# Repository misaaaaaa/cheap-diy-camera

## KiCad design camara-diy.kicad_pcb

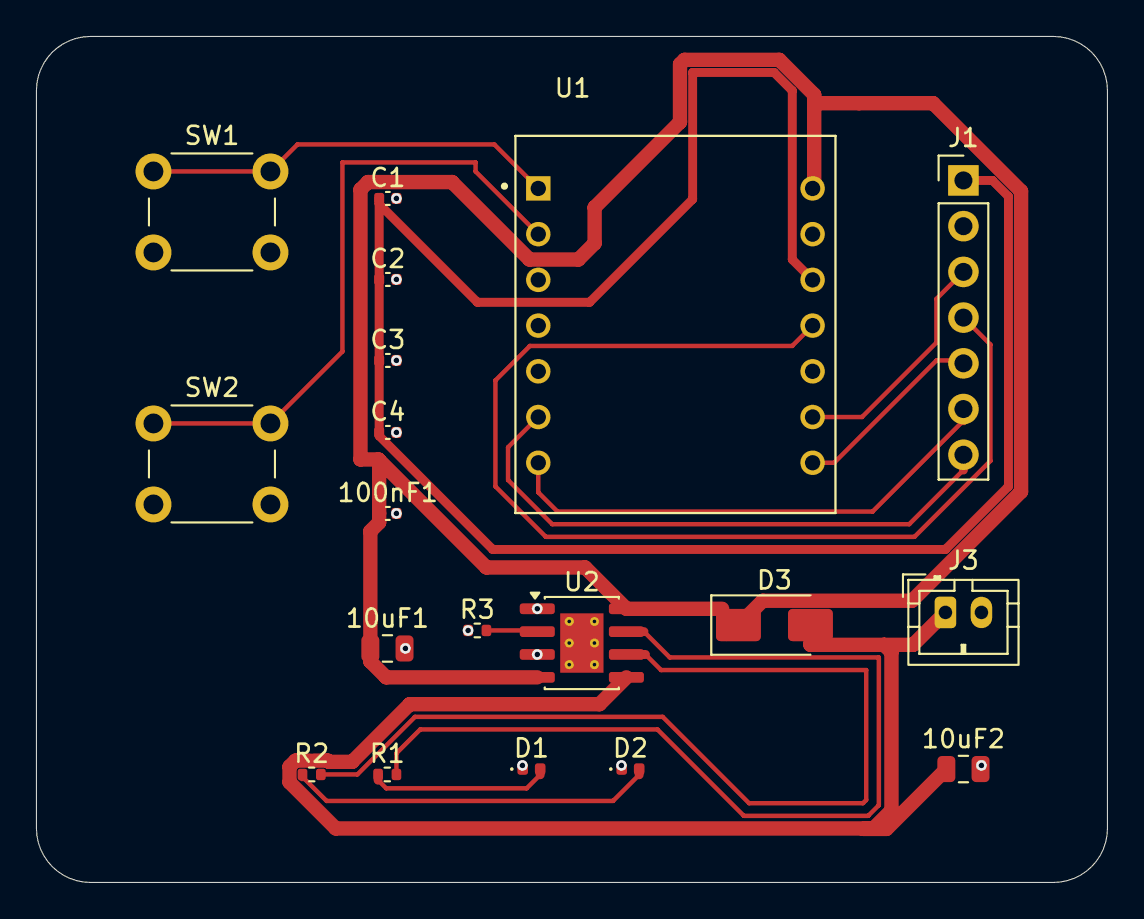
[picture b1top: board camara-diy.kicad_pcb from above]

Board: 2 copper layers, 59.5 x 47.0 mm, 19 parts (0 on the bottom side), 16 nets.

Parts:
10uF1: C6; C_0805_2012Metric
10uF2: C7; C_0805_2012Metric
100nF1: C5; C_0402_1005Metric
C1, C2, C3, C4: C; C_0402_1005Metric
D1, D2: LED; LED_0402_1005Metric
D3: D_Schottky; D_SMA
J1: Conn_01x07; PinHeader_1x07_P2.54mm_Vertical
J3: Conn_01x02; JST_PH_B2B-PH-K_1x02_P2.00mm_Vertical
R1, R2: R; R_0402_1005Metric
R3: 2k; R_0402_1005Metric
SW1, SW2: SW_Push; SW_PUSH_6mm_H5mm
U1: XIAO-ESP32-S3-SMD; MODULE_113991054
U2: TP4056-42-ESOP8; SOIC-8-1EP_3.9x4.9mm_P1.27mm_EP2.41x3.3mm_ThermalVias

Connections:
+3V3: C1.1, C2.1, C3.1, C4.1, J1.1, U1.12 (3V3)
+5V: 10uF1.1, 100nF1.1, D3.1 (K), U1.14 (5V), U2.4 (V_{CC}), U2.8 (CE)
/BAT_18650: 10uF2.1, D3.2 (A), J3.1, U2.5 (BAT)
/BTN_MODO: SW2.1, U1.2 (GPIO2_A1_D1)
/BTN_SHUTTER: SW1.1, U1.1 (GPIO1_A0_D0)
/DISP_CS: J1.7, U1.6 (GPIO6_A5_D5_SCL)
/DISP_DC: J1.6, U1.7 (GPIO43_A6_D6_TX)
/DISP_RES: J1.5, U1.8 (GPIO44_D7_RX)
/SPI_CLK: J1.3, U1.9 (GPIO7_A8_D8_SCK)
/SPI_MOSI: J1.4, U1.11 (GPIO9_A10_D10_MOSI)
GND: 10uF1.2, 10uF2.2, 100nF1.2, C1.2, C2.2, C3.2, C4.2, D1.1 (K), D2.1 (K), J1.2, J3.2, R3.1, SW1.2, SW2.2, U1.13 (GND), U2.1 (TEMP), U2.3 (GND), U2.9 (EPAD)
unnamed: D1.2 (A), R1.1
unnamed: D2.2 (A), R2.1
unnamed: R3.2, U2.2 (PROG)
unnamed: R1.2, U2.7 (~CHRG)
unnamed: R2.2, U2.6 (~STDBY)

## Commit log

2026-03-15 editados DRC
